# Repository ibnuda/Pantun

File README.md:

# Pantun

A Prime-E / 40% Alice-style keyboard for IMKG Joglosemarkarto Chapter.

## About the name
Pantun (Jawi: ڤنتون) is a Malay oral poetic form used to express intricate ideas and emotions.
It is generally consists of even-numbered lines and based on ABAB rhyming schemes.

## My plea
If somehow you fabricate this design, I hope that you feed a filling meal to one
of your less-fortunate neighbours.

## License
CERN Open Hardware Licence Version 2 - Strongly Reciprocal

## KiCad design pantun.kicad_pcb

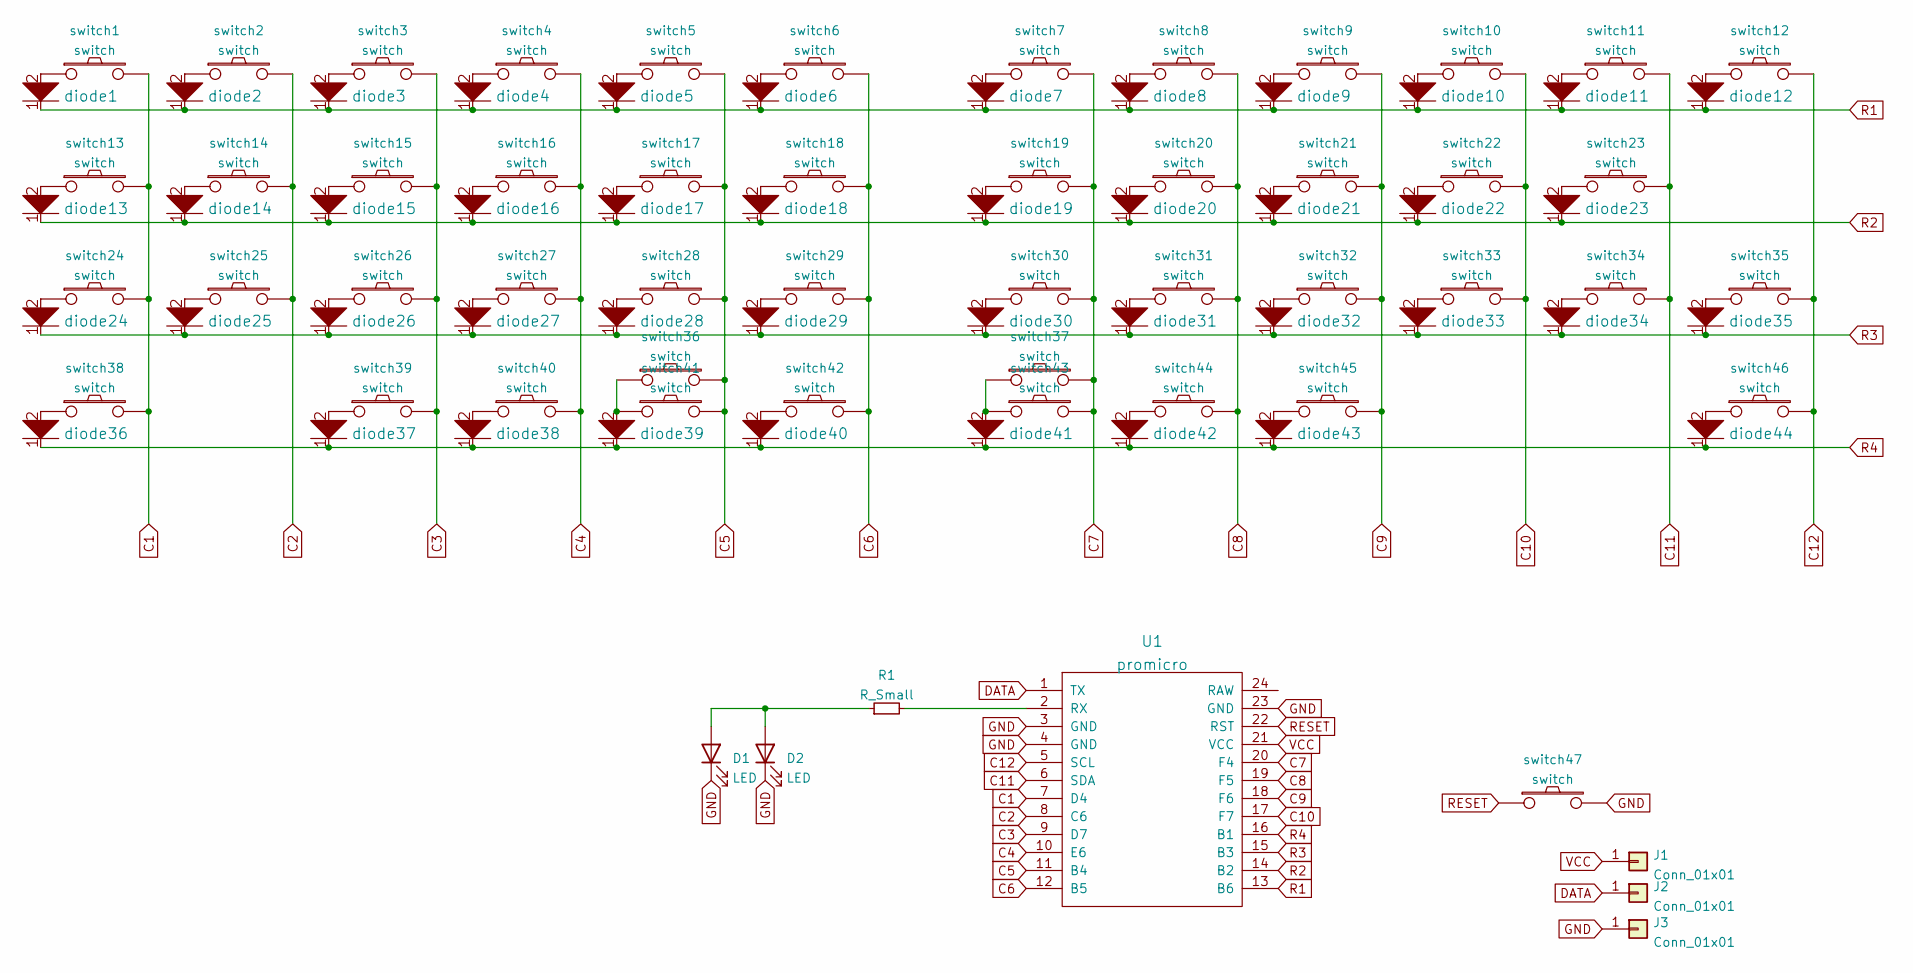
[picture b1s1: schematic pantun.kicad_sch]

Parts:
D1, D2: LED; LED_D2.0mm_W4.0mm_H2.8mm_FlatTop
J1, J2, J3: Conn_01x01; wirepad
R1: R_Small; R_Box_L8.4mm_W2.5mm_P5.08mm
U1: promicro; promicro-flip
diode1, diode2, diode3, diode4, diode5, diode6, diode7, diode8, diode9, diode10, diode11, diode12, diode13, diode14, diode15, diode16, diode17, diode18, diode19, diode20, diode21, diode22, diode23, diode24, diode25, diode26, diode27, diode28, diode29, diode30, diode31, diode32, diode33, diode34, diode35, diode36, diode37, diode38, diode39, diode40, diode41, diode42, diode43, diode44: diode; diode-sod-123
switch1, switch2, switch3, switch4, switch5, switch6, switch7, switch8, switch9, switch10, switch11, switch12, switch14, switch15, switch16, switch17, switch18, switch19, switch20, switch21, switch22, switch25, switch26, switch27, switch28, switch29, switch30, switch31, switch32, switch33, switch34, switch39, switch40, switch41, switch42, switch45: switch; 100-socket-solder
switch13, switch35, switch44: switch; 125-socket-solder
switch23, switch24: switch; 175-socket-solder
switch36: switch; 200-socket-solder
switch37: switch; 275-socket-solder
switch38, switch43, switch46: switch; 150-socket-solder
switch47: switch; reset

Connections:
C1: U1.7 (D4), switch1.2, switch13.2, switch24.2, switch38.2
C2: U1.8 (C6), switch2.2, switch14.2, switch25.2
C3: U1.9 (D7), switch3.2, switch15.2, switch26.2, switch39.2
C4: U1.10 (E6), switch4.2, switch16.2, switch27.2, switch40.2
C5: U1.11 (B4), switch5.2, switch17.2, switch28.2, switch36.2, switch41.2
C6: U1.12 (B5), switch6.2, switch18.2, switch29.2, switch42.2
C7: U1.20 (F4), switch7.2, switch19.2, switch30.2, switch37.2, switch43.2
C8: U1.19 (F5), switch8.2, switch20.2, switch31.2, switch44.2
C9: U1.18 (F6), switch9.2, switch21.2, switch32.2, switch45.2
C10: U1.17 (F7), switch10.2, switch22.2, switch33.2
C11: U1.6 (SDA), switch11.2, switch23.2, switch34.2
C12: U1.5 (SCL), switch12.2, switch35.2, switch46.2
DATA: J2.1, U1.1 (TX)
GND: D1.1 (K), D2.1 (K), J3.1, U1.3 (GND), U1.4 (GND), U1.23 (GND), switch47.2
unnamed: D1.2 (A), D2.2 (A), R1.1
unnamed: R1.2, U1.2 (RX)
unnamed: diode1.2, switch1.1
unnamed: diode2.2, switch2.1
unnamed: diode3.2, switch3.1
unnamed: diode4.2, switch4.1
unnamed: diode5.2, switch5.1
unnamed: diode6.2, switch6.1
unnamed: diode7.2, switch7.1
unnamed: diode8.2, switch8.1
unnamed: diode9.2, switch9.1
unnamed: diode10.2, switch10.1
unnamed: diode11.2, switch11.1
unnamed: diode12.2, switch12.1
unnamed: diode13.2, switch13.1
unnamed: diode14.2, switch14.1
unnamed: diode15.2, switch15.1
unnamed: diode16.2, switch16.1
unnamed: diode17.2, switch17.1
unnamed: diode18.2, switch18.1
unnamed: diode19.2, switch19.1
unnamed: diode20.2, switch20.1
unnamed: diode21.2, switch21.1
unnamed: diode22.2, switch22.1
unnamed: diode23.2, switch23.1
unnamed: diode24.2, switch24.1
unnamed: diode25.2, switch25.1
unnamed: diode26.2, switch26.1
unnamed: diode27.2, switch27.1
unnamed: diode28.2, switch28.1
unnamed: diode29.2, switch29.1
unnamed: diode30.2, switch30.1
unnamed: diode31.2, switch31.1
unnamed: diode32.2, switch32.1
unnamed: diode33.2, switch33.1
unnamed: diode34.2, switch34.1
unnamed: diode35.2, switch35.1
unnamed: diode36.2, switch38.1
unnamed: diode37.2, switch39.1
unnamed: diode38.2, switch40.1
unnamed: diode39.2, switch36.1, switch41.1
unnamed: diode40.2, switch42.1
unnamed: diode41.2, switch37.1, switch43.1
unnamed: diode42.2, switch44.1
unnamed: diode43.2, switch45.1
unnamed: diode44.2, switch46.1
R1: U1.13 (B6), diode1.1, diode2.1, diode3.1, diode4.1, diode5.1, diode6.1, diode7.1, diode8.1, diode9.1, diode10.1, diode11.1, diode12.1
R2: U1.14 (B2), diode13.1, diode14.1, diode15.1, diode16.1, diode17.1, diode18.1, diode19.1, diode20.1, diode21.1, diode22.1, diode23.1
R3: U1.15 (B3), diode24.1, diode25.1, diode26.1, diode27.1, diode28.1, diode29.1, diode30.1, diode31.1, diode32.1, diode33.1, diode34.1, diode35.1
R4: U1.16 (B1), diode36.1, diode37.1, diode38.1, diode39.1, diode40.1, diode41.1, diode42.1, diode43.1, diode44.1
RESET: U1.22 (RST), switch47.1
VCC: J1.1, U1.21 (VCC)

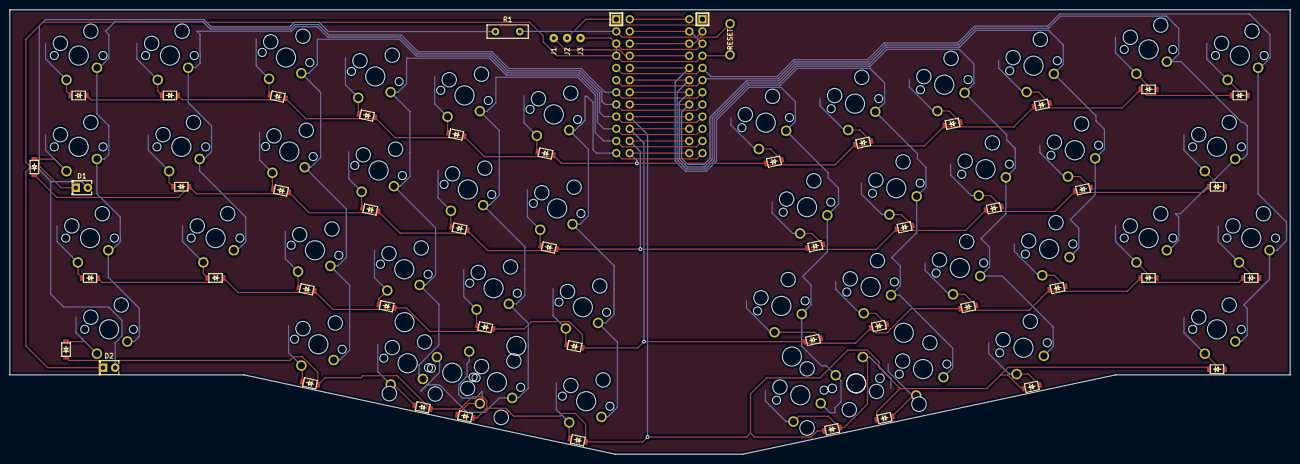
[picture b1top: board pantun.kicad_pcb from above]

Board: 2 copper layers, 267.3 x 92.8 mm, 98 parts (0 on the bottom side), 66 nets.

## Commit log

2022-02-06 init commit.
2022-02-06 moved thumb row 1/4u to the left and added one 1u.
2022-02-06 added stacked acrylic plates.
2022-02-06 HOOOOOOOOOOOOAAAAAAAAAAAAAAGGGGGGGGGGGGGGGGHHHHHHHHHHHHHH!!!!
2022-02-07 added led. lol.
